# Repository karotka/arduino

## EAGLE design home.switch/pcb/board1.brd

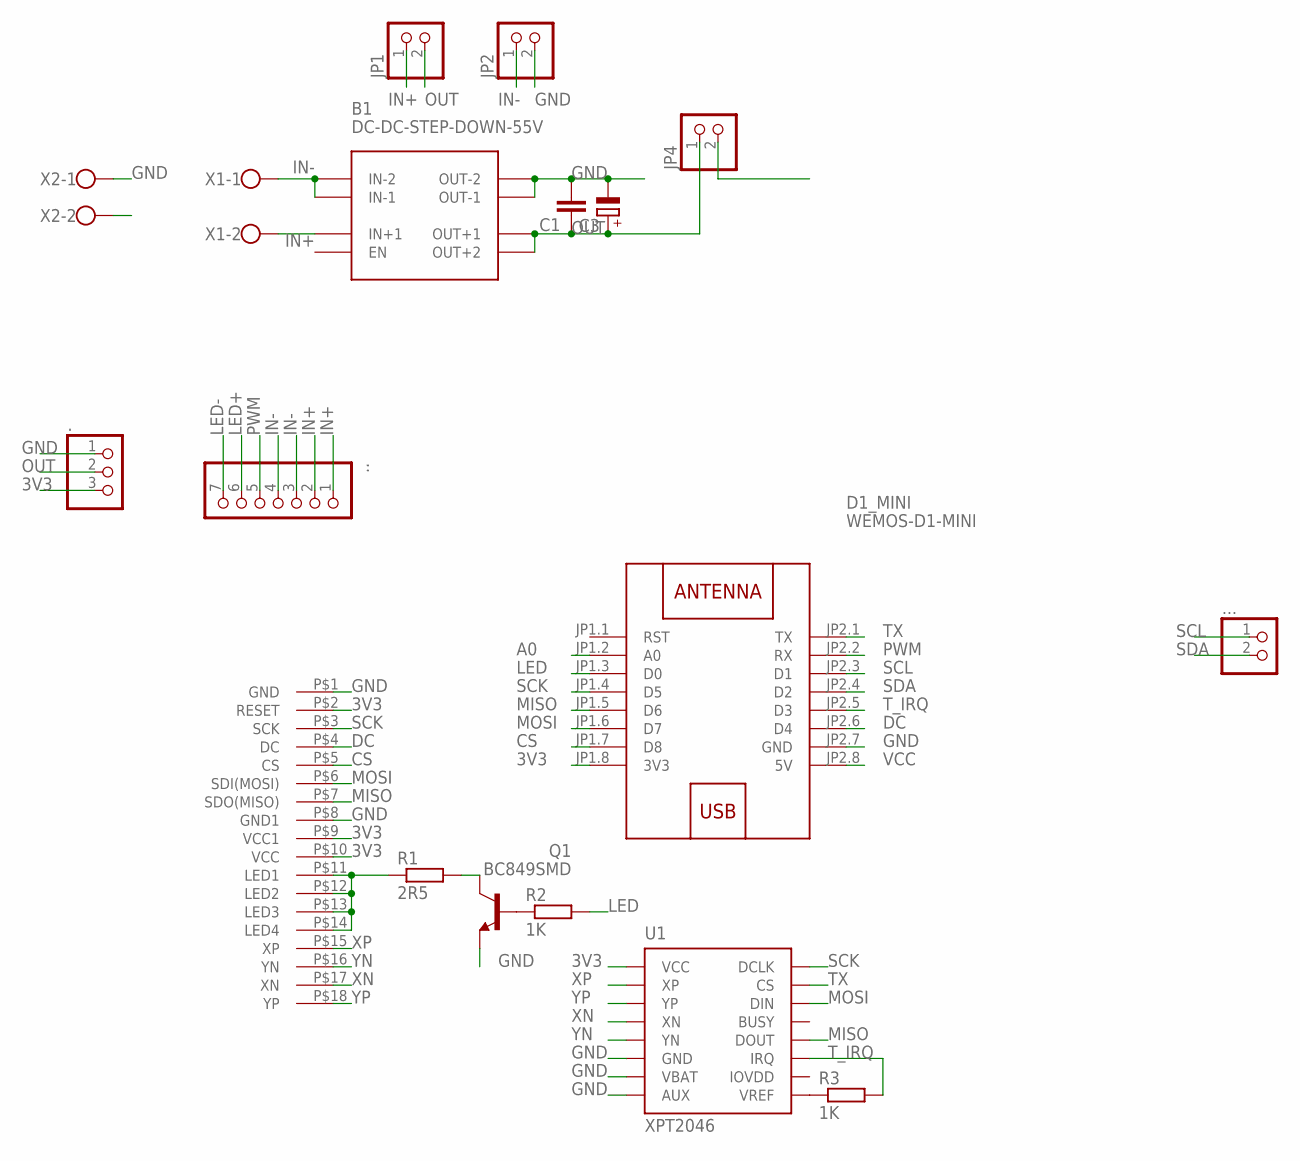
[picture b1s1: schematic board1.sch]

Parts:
.: PINHD-1X3; 1X03
..: PINHD-1X7; 1X07
...: PINHD-1X2; 1X02
B1: DC-DC-STEP-DOWN-55V
C1: C-EUC0805; C0805
C3: CPOL-EUE2-5; E2-5
D1_MINI: WEMOS-D1-MINI
JP1, JP2, JP4: PINHD-1X2; 1X02
Q1: BC849SMD; SOT23-BEC
R1: 2R5; R1210W
R2, R3: 1K; R1210W
U1: XPT2046; TSSOP16
U$2: 2.4TTF; TFT2.4
X1, X2: W237-102

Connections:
3V3: ..3, D1_MINI.JP1.8 (3V3), U1.1 (VCC), U$2.P$2 (RESET), U$2.P$9 (VCC1), U$2.P$10 (VCC)
A0: D1_MINI.JP1.2 (A0), X2.2
CS: D1_MINI.JP1.7 (D8), U$2.P$5 (CS)
DC: D1_MINI.JP2.6 (D4), U$2.P$4 (DC)
GND: ..1, B1.VOUT-1 (OUT-1), B1.VOUT-2 (OUT-2), C1.2, C3.-, D1_MINI.JP2.7 (GND), JP2.2, Q1.E, U1.6 (GND), U1.7 (VBAT), U1.8 (AUX), U$2.P$1 (GND), U$2.P$8 (GND1), X2.1
IN+: ...1, ...2, B1.VIN+ (IN+1), JP1.1, X1.2
IN-: ...3, ...4, B1.VIN-1 (IN-1), B1.VIN-2 (IN-2), JP2.1, X1.1
LED: D1_MINI.JP1.3 (D0), R2.2
LED+: ...6
LED-: ...7
MISO: D1_MINI.JP1.5 (D6), U1.12 (DOUT), U$2.P$7 (SDO(MISO))
MOSI: D1_MINI.JP1.6 (D7), U1.14 (DIN), U$2.P$6 (SDI(MOSI))
unnamed: R1.1, U$2.P$11 (LED1), U$2.P$12 (LED2), U$2.P$13 (LED3), U$2.P$14 (LED4)
unnamed: Q1.C, R1.2
unnamed: Q1.B, R2.1
unnamed: R3.1, U1.9 (VREF)
OUT: ..2, B1.VOUT+1 (OUT+1), B1.VOUT+2 (OUT+2), C1.1, C3.+, JP1.2, JP4.1
PWM: ...5, D1_MINI.JP2.2 (RX)
SCK: D1_MINI.JP1.4 (D5), U1.16 (DCLK), U$2.P$3 (SCK)
SCL: ....1, D1_MINI.JP2.3 (D1)
SDA: ....2, D1_MINI.JP2.4 (D2)
TX: D1_MINI.JP2.1 (TX), U1.15 (CS)
T_IRQ: D1_MINI.JP2.5 (D3), R3.2, U1.11 (IRQ)
VCC: D1_MINI.JP2.8 (5V), JP4.2
XN: U1.4 (XN), U$2.P$17 (XN)
XP: U1.2 (XP), U$2.P$15 (XP)
YN: U1.5 (YN), U$2.P$16 (YN)
YP: U1.3 (YP), U$2.P$18 (YP)

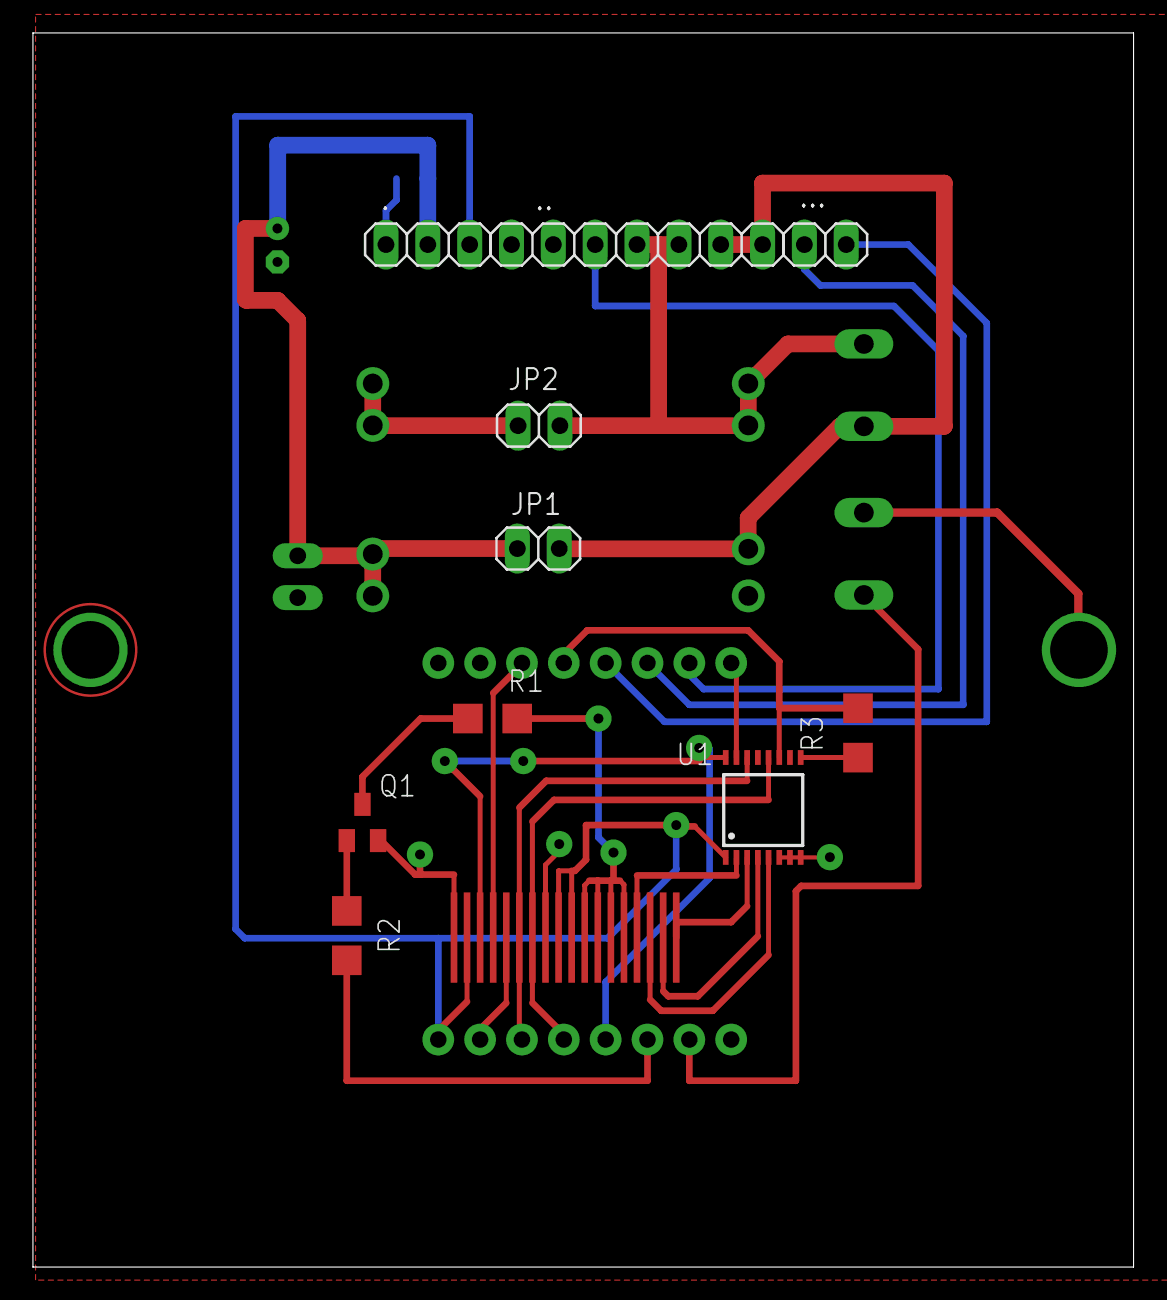
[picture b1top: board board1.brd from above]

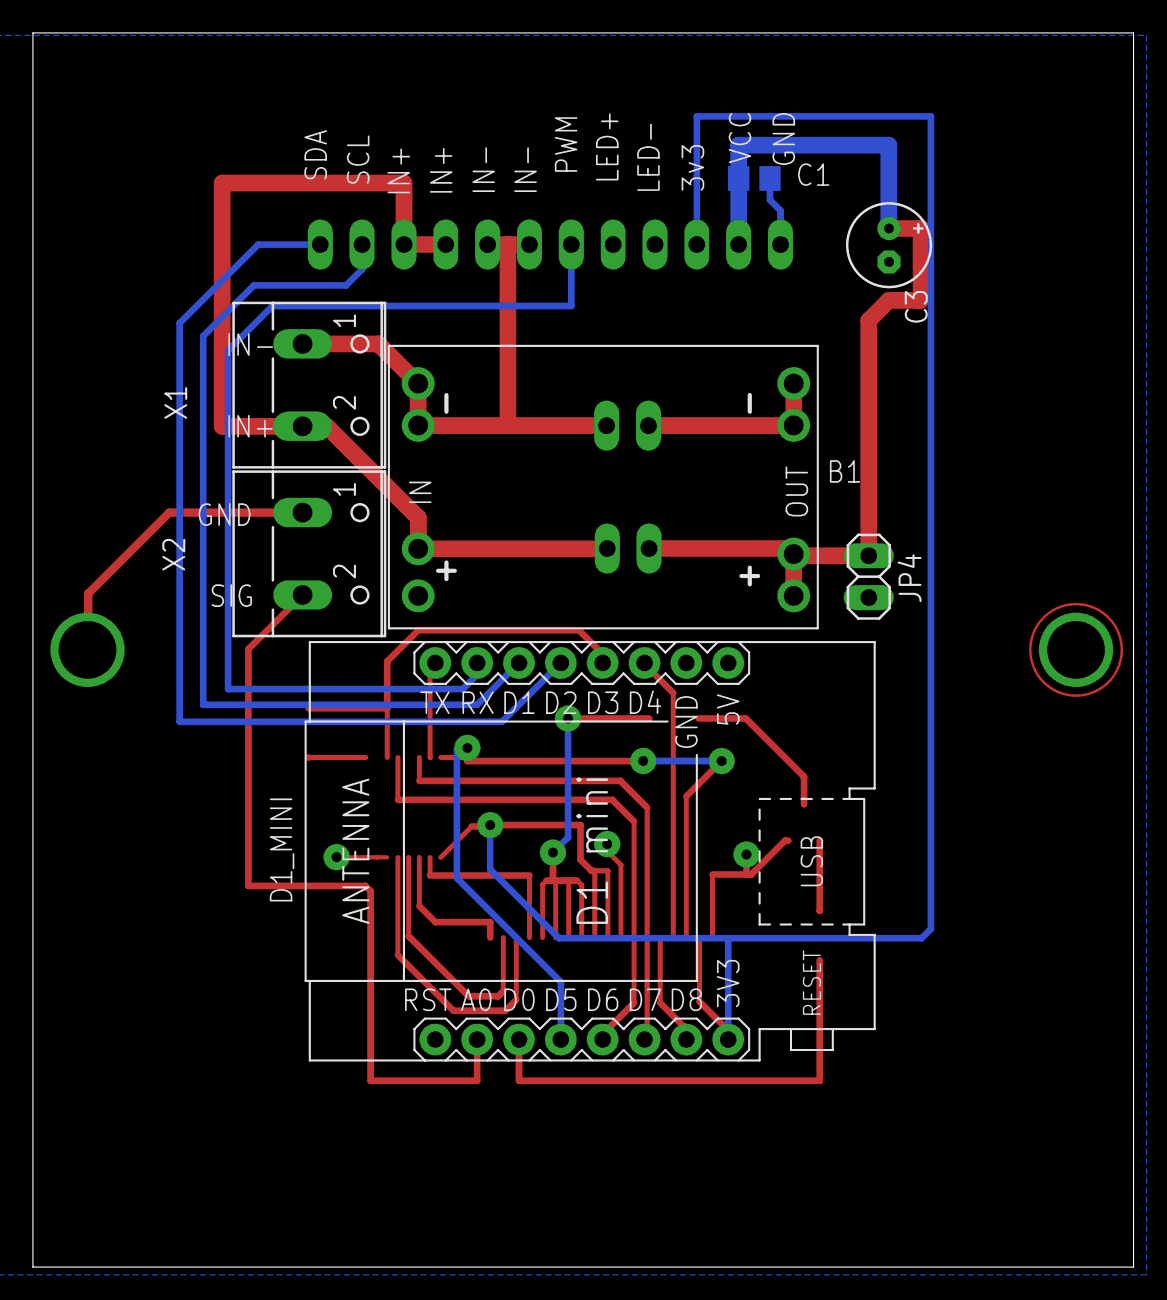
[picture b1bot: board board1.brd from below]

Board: 2 copper layers, 66.8 x 74.9 mm, 18 parts (7 on the bottom side), 26 nets.

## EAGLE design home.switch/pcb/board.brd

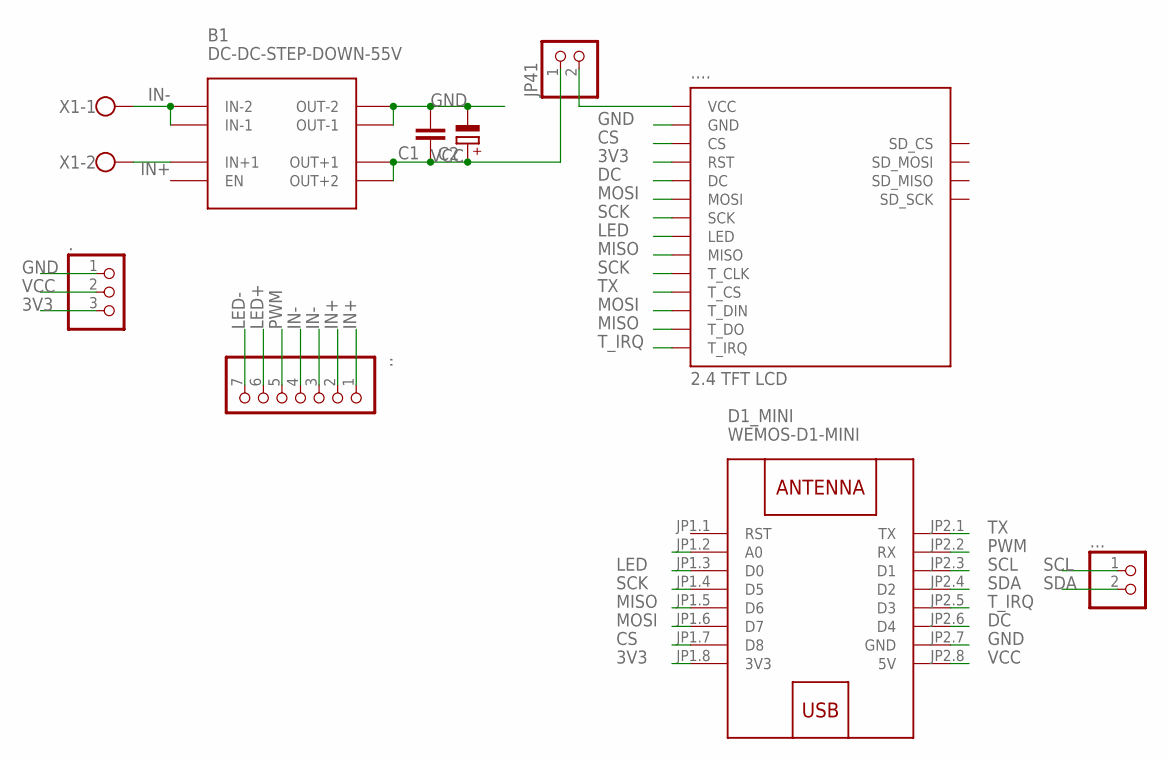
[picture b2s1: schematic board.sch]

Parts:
.: PINHD-1X3; 1X03
..: PINHD-1X7; 1X07
...: PINHD-1X2; 1X02
....: 2.2_TFT_LCD
B1: DC-DC-STEP-DOWN-55V
C1: C-EUC0805; C0805
C2: CPOL-EUE2-5; E2-5
D1_MINI: WEMOS-D1-MINI
JP41: PINHD-1X2; 1X02
X1: W237-102

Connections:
3V3: ..3, .....RST, D1_MINI.JP1.8 (3V3)
CS: .....CS, D1_MINI.JP1.7 (D8)
DC: .....DC, D1_MINI.JP2.6 (D4)
GND: ..1, .....GND, B1.VOUT-1 (OUT-1), B1.VOUT-2 (OUT-2), C1.2, C2.-, D1_MINI.JP2.7 (GND)
IN+: ...1, ...2, B1.VIN+ (IN+1), X1.2
IN-: ...3, ...4, B1.VIN-1 (IN-1), B1.VIN-2 (IN-2), X1.1
LED: .....LED, D1_MINI.JP1.3 (D0)
LED+: ...6
LED-: ...7
MISO: .....MISO, .....T_DO, D1_MINI.JP1.5 (D6)
MOSI: .....MOSI, .....T_DIN, D1_MINI.JP1.6 (D7)
unnamed: .....VCC, JP41.2
PWM: ...5, D1_MINI.JP2.2 (RX)
SCK: .....SCK, .....T_CLK, D1_MINI.JP1.4 (D5)
SCL: ....1, D1_MINI.JP2.3 (D1)
SDA: ....2, D1_MINI.JP2.4 (D2)
TX: .....T_CS, D1_MINI.JP2.1 (TX)
T_IRQ: .....T_IRQ, D1_MINI.JP2.5 (D3)
VCC: ..2, B1.VOUT+1 (OUT+1), B1.VOUT+2 (OUT+2), C1.1, C2.+, D1_MINI.JP2.8 (5V), JP41.1

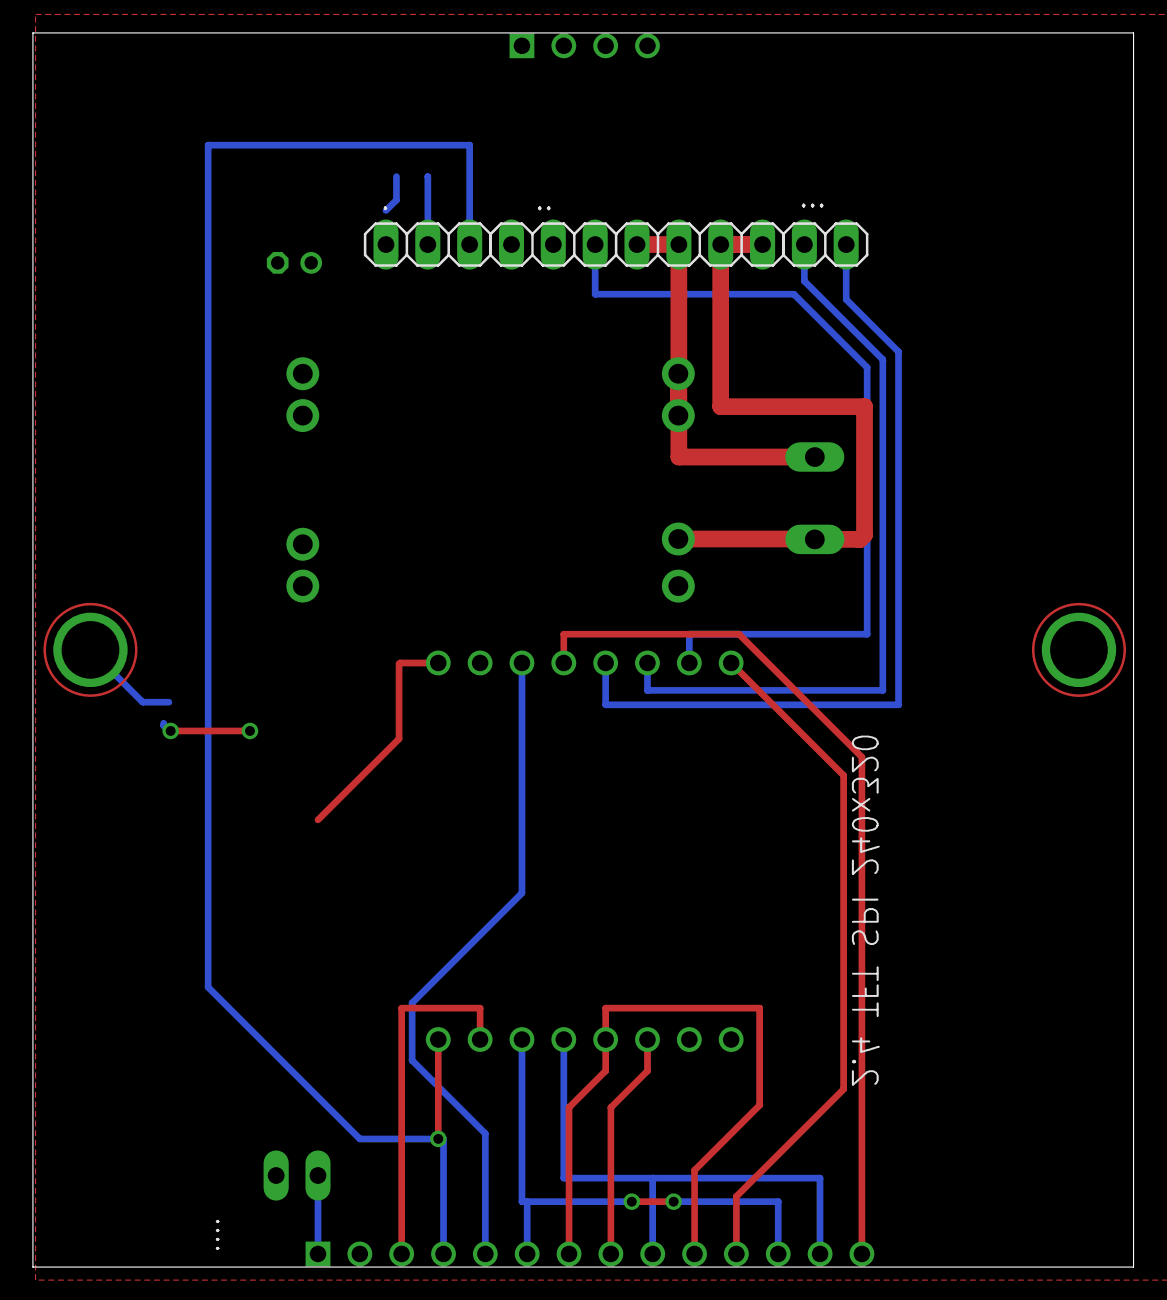
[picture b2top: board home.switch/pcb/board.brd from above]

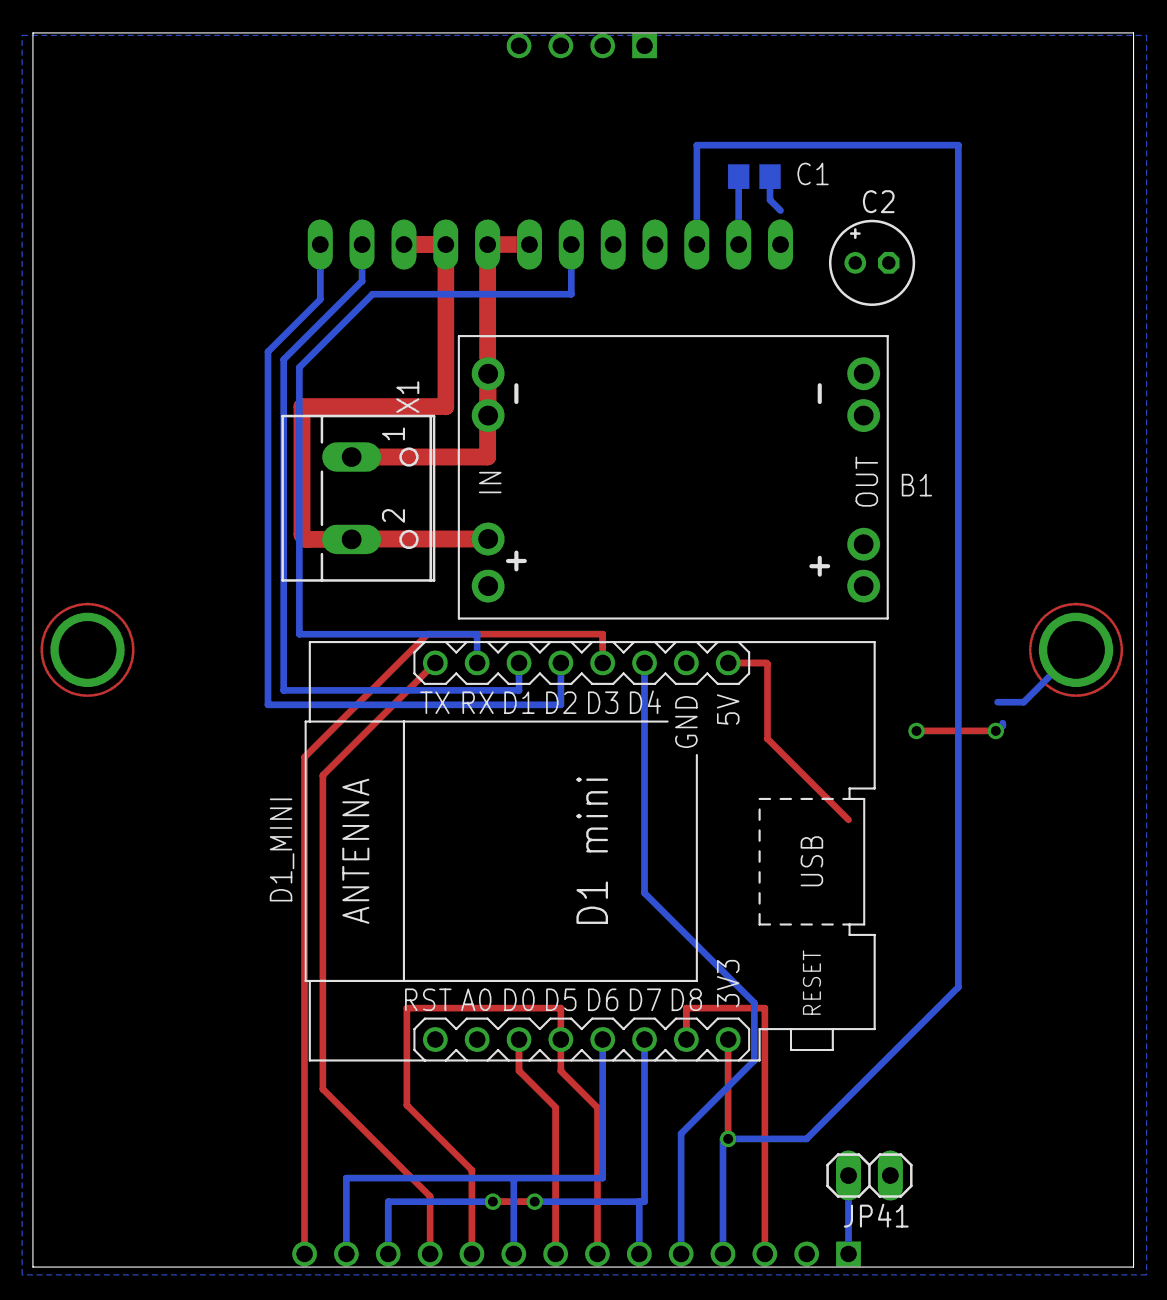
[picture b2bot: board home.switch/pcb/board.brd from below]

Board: 2 copper layers, 66.8 x 74.9 mm, 10 parts (6 on the bottom side), 17 nets.

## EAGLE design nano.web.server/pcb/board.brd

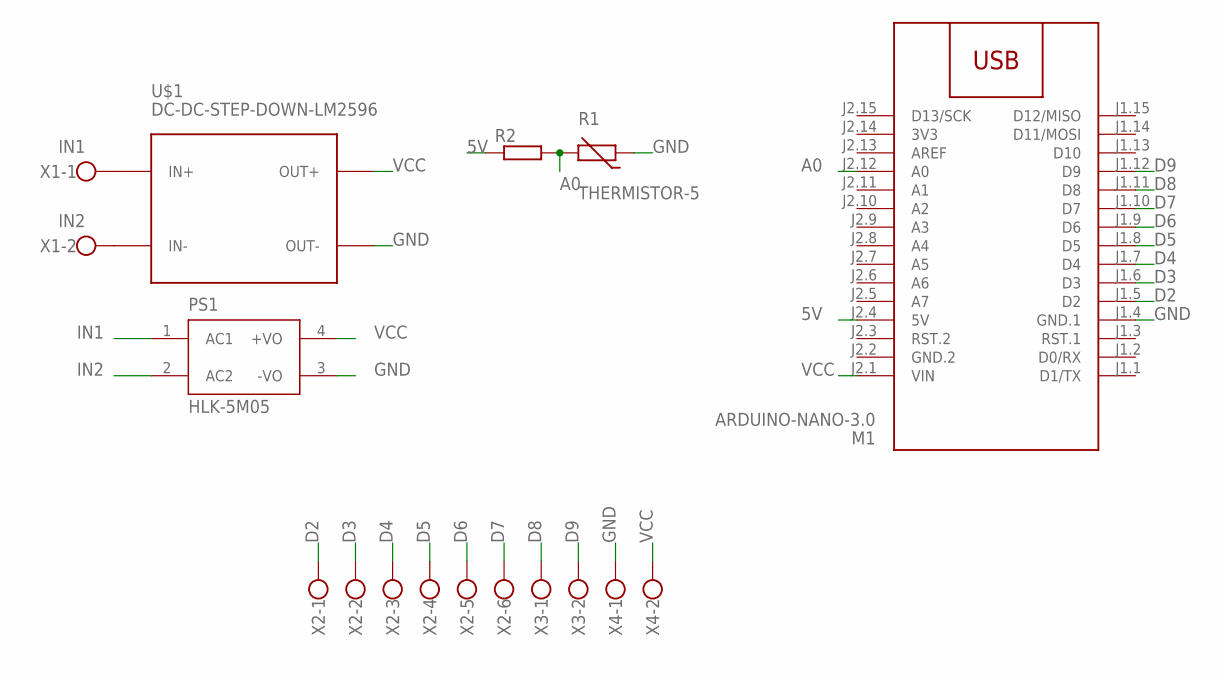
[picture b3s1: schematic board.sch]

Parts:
M1: ARDUINO-NANO-3.0
PS1: HLK-5M05; CONV_HLK-5M05
R1: THERMISTOR-5; R-5
R2: R-EU_0207/10; 0207/10
U$1: DC-DC-STEP-DOWN-LM2596
X1, X3, X4: W237-102
X2: W237-136

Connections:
3V3: M1.J2.14 (3V3)
5V: M1.J2.4 (5V), R2.1
A0: M1.J2.12 (A0), R1.2, R2.2
D2: M1.J1.5 (D2), X2.1
D3: M1.J1.6 (D3), X2.2
D4: M1.J1.7 (D4), X2.3
D5: M1.J1.8 (D5), X2.4
D6: M1.J1.9 (D6), X2.5
D7: M1.J1.10 (D7), X2.6
D8: M1.J1.11 (D8), X3.1
D9: M1.J1.12 (D9), X3.2
GND: M1.J1.4 (GND.1), PS1.3 (-VO), R1.1, U$1.OUT-, X4.1
GND.2: M1.J2.2 (GND.2)
IN1: PS1.1 (AC1), U$1.IN+, X1.1
IN2: PS1.2 (AC2), U$1.IN-, X1.2
VCC: M1.J2.1 (VIN), PS1.4 (+VO), U$1.OUT+, X4.2

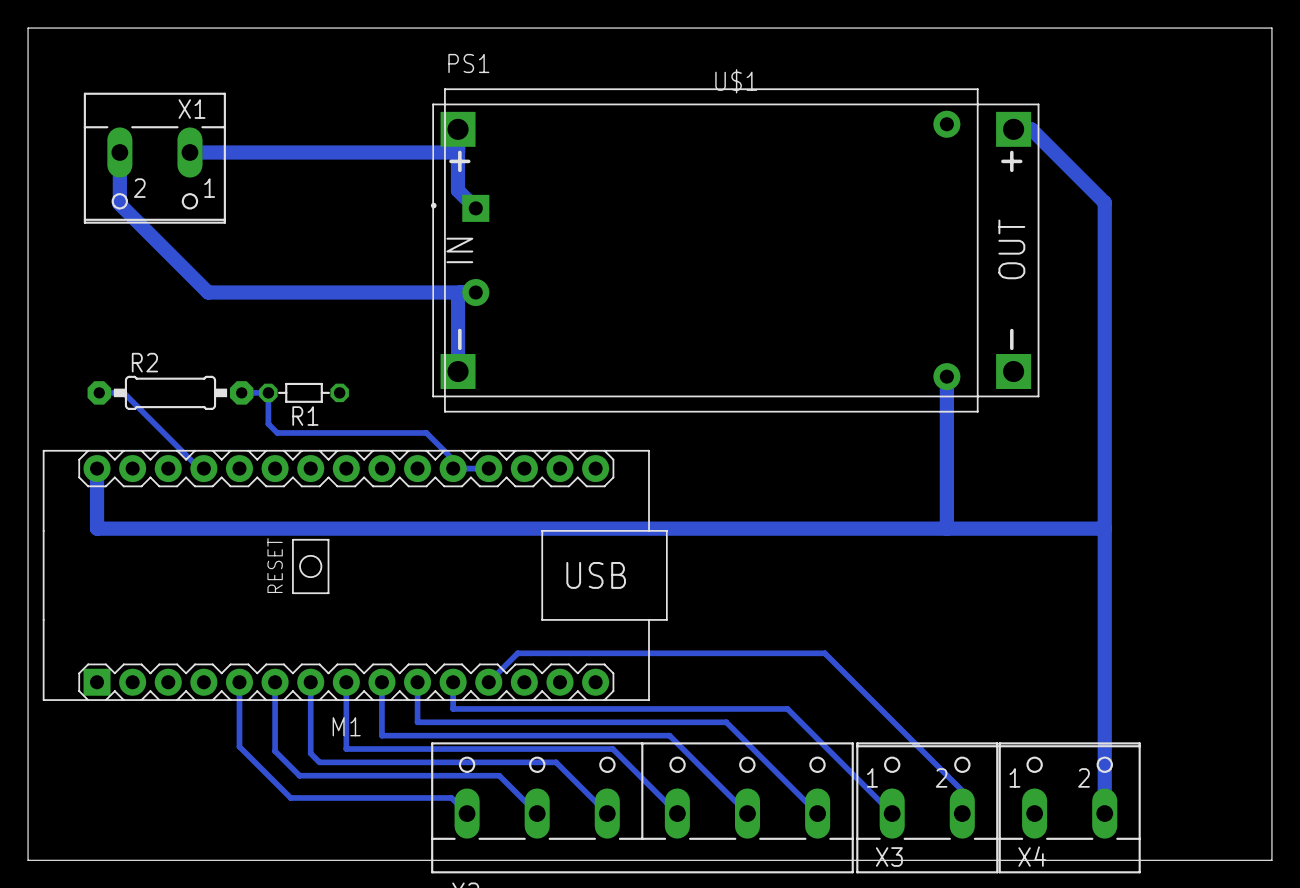
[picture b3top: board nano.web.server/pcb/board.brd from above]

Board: 2 copper layers, 88.7 x 59.4 mm, 9 parts (0 on the bottom side), 14 nets.

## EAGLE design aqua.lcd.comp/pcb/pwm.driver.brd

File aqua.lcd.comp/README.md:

Aquarium computer
=================

Properties
----------

2018-08-21:
	Actually I working on new shield for Arduino Mega with serial display connection, web interface with (Microsoft Metro design) Esp8266 and other new features 

- Computer for manage aquarium lights and measurment the tempereature

It is possible to set many modes of change light color in time.

- Date and time

It containts on board RTC clock for date and time measurment

- Touch display

You can manage all function by touch display

- 6 independent light channels with PWM

you can manage 6 lights channel for to set you onw 12V LED lights

- 8 independent light modes

can manage your onw day lights modes

- rele for switching 230V for CO2 valve switching

- 3 independent sensor for temperature measurment

3 thermistor channels can measure temperature in different position in aquarium

- 1 onboard sensor for temperature measurment

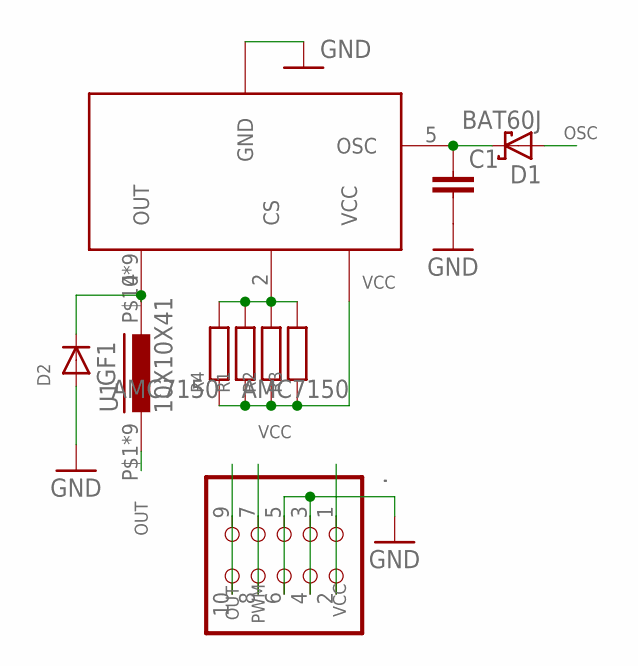
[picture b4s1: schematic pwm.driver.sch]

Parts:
.: PINHD-2X5; 2X05
AMC7150: AMC7150; TO-252-5L
C1: C-EU025-024X044; C025-024X044
D1: BAT60J; SOD323_ST
D2: GF1; SMA-DO214AC
R1, R2, R3, R4: R-EU_R1206; R1206
U1: 10X10X41; 10X10X4

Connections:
CS: AMC7150.2 (CS), R1.2, R2.2, R3.2, R4.2
GND: ..3, ..4, ..5, ..6, AMC7150.3 (GND), AMC7150.TAB (GND), C1.2, D2.A
unnamed: AMC7150.4 (OUT), D2.K (C), U1.P$10 (2), U1.P$11 (2), U1.P$12 (2), U1.P$13 (2), U1.P$14 (2), U1.P$15 (2), U1.P$16 (2), U1.P$17 (2), U1.P$18 (2)
OSC: AMC7150.5 (OSC), C1.1, D1.C
OUT: ..9, ..10, U1.P$1 (1), U1.P$2 (1), U1.P$3 (1), U1.P$4 (1), U1.P$5 (1), U1.P$6 (1), U1.P$7 (1), U1.P$8 (1), U1.P$9 (1)
PWM: ..7, ..8, D1.A
VCC: ..1, ..2, AMC7150.1 (VCC), R1.1, R2.1, R3.1, R4.1

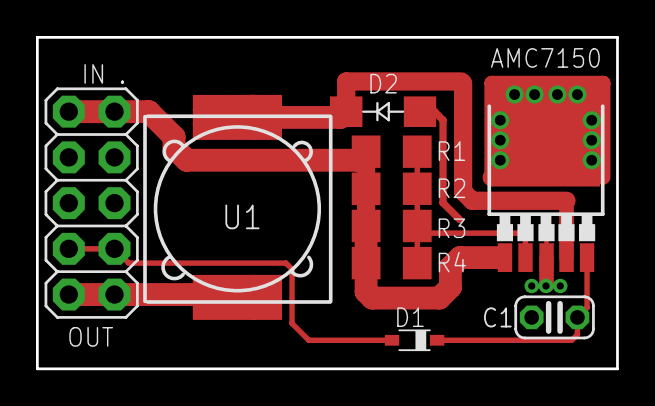
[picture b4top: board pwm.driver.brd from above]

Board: 2 copper layers, 32.2 x 18.4 mm, 10 parts (0 on the bottom side), 7 nets.

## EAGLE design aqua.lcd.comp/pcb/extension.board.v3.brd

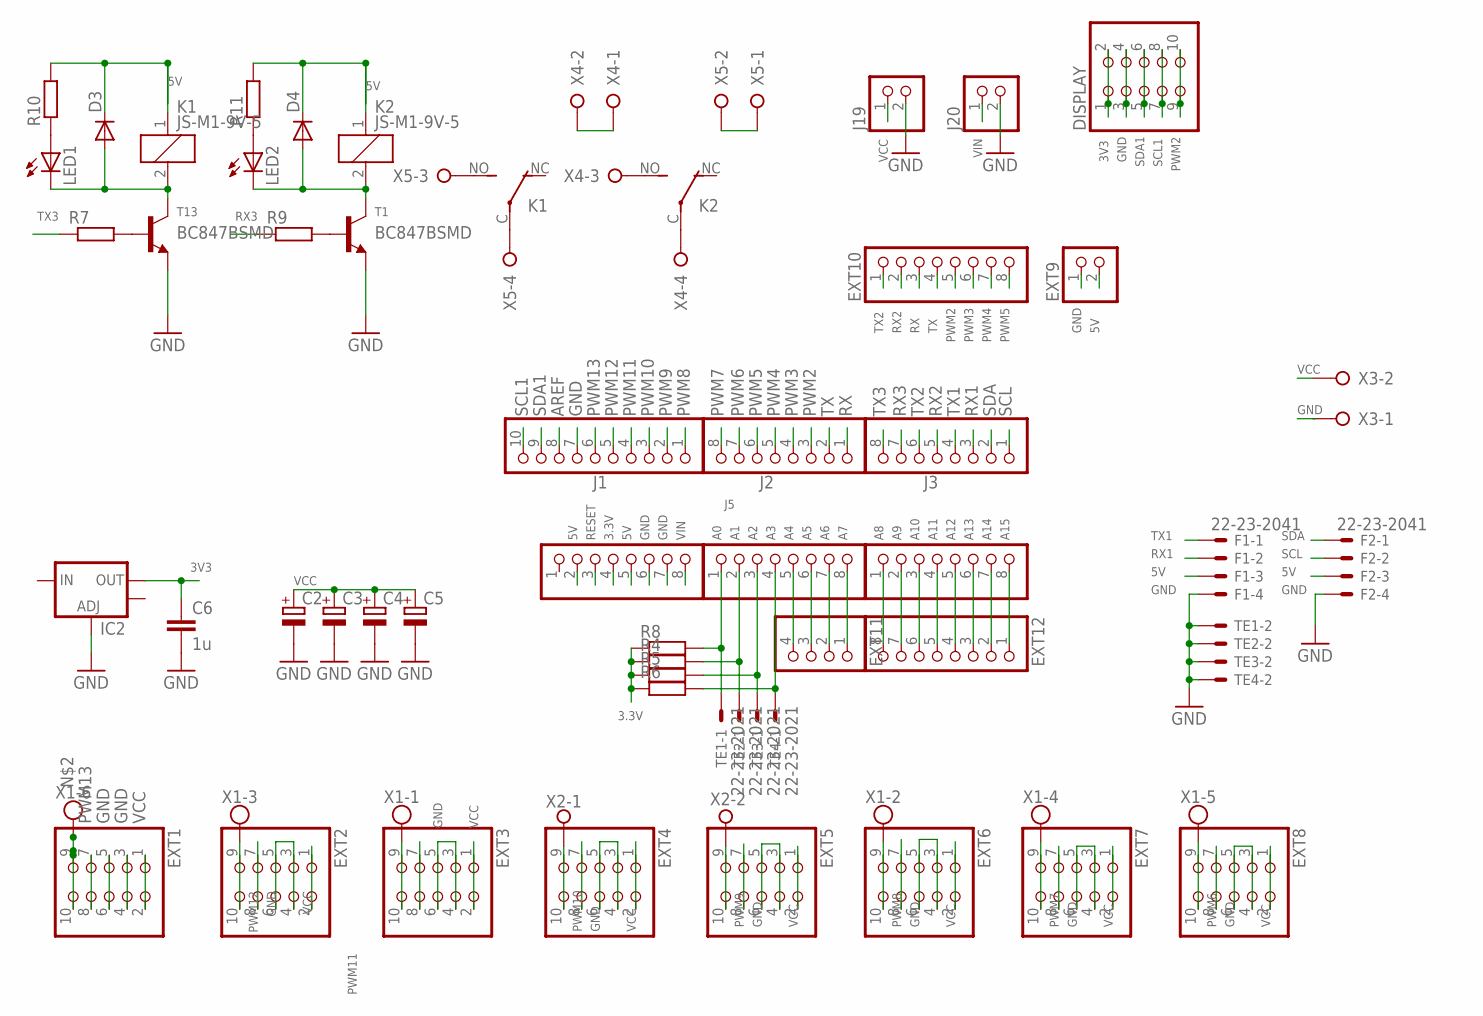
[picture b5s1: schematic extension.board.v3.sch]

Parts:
C2, C3, C4, C5: CPOL-EUE2.5-7; E2,5-7
C6: 1u; C0805
D3, D4: DIODE-DO-214AC; DO-214AC
DISPLAY: PINHD-2X5; 2X05
EXT1, EXT2, EXT3, EXT4, EXT5, EXT6, EXT7, EXT8: PINHD-2X5; 2X05
EXT9: PINHD-1X2; 1X02
EXT10, EXT12: PINHD-1X8; 1X08
EXT11: PINHD-1X4; 1X04
F1, F2: 22-23-2041
IC2: V_REG_LM1117SOT223; SOT223
J1: PINHD-1X10; 1X10
J2, J3, J4, J5, J6: PINHD-1X8; 1X08
J19, J20: PINHD-1X2; 1X02
K1, K2: JS-M1-9V-5; JS-M
LED1, LED2: LEDSML1206; SML1206
R4, R5, R6, R7, R8, R9, R10, R11: R-EU_R1206; R1206
T1, T13: BC847BSMD; SOT23
TE1, TE2, TE3, TE4: 22-23-2021
X1: W237-6
X2, X3: W237-02P; W237-132
X4, X5: W237-04P; W237-4P

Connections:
3.3V: J6.4, R4.1, R5.1, R6.1, R8.1
3V3: C6.1, DISPLAY.1, DISPLAY.2, IC2.2 (OUT)
5V: D3.C, D4.C, EXT9.2, F1.3, F2.3, J6.2, J6.5, K1.1, K2.1, R10.2, R11.2
A0: J5.1, R8.2, TE1.1
A1: J5.2, R4.2, TE2.1
A2: J5.3, R5.2, TE3.1
A3: J5.4, R6.2, TE4.1
A4: EXT11.4, J5.5
A5: EXT11.3, J5.6
A6: EXT11.2, J5.7
A7: EXT11.1, J5.8
A8: EXT12.8, J4.1
A9: EXT12.7, J4.2
A10: EXT12.6, J4.3
A11: EXT12.5, J4.4
A12: EXT12.4, J4.5
A13: EXT12.3, J4.6
A14: EXT12.2, J4.7
A15: EXT12.1, J4.8
AREF: J1.8
GND: C2.-, C3.-, C4.-, C5.-, C6.2, DISPLAY.3, DISPLAY.4, EXT1.3, EXT1.4, EXT1.5, EXT1.6, EXT2.3, EXT2.4, EXT2.5, EXT2.6, EXT3.3, EXT3.4, EXT3.5, EXT3.6, EXT4.3, EXT4.4, EXT4.5, EXT4.6, EXT5.3, EXT5.4, EXT5.5, EXT5.6, EXT6.3, EXT6.4, EXT6.5, EXT6.6, EXT7.3, EXT7.4, EXT7.5, EXT7.6, EXT8.3, EXT8.4, EXT8.5, EXT8.6, EXT9.1, F1.4, F2.4, IC2.1 (ADJ), J1.7, J6.6, J6.7, J19.2, J20.2, T1.2 (E), T13.2 (E), TE1.2, TE2.2, TE3.2, TE4.2, X3.1
unnamed: EXT1.9, EXT1.10, X1.6
unnamed: EXT8.9, EXT8.10, X1.5
unnamed: EXT7.9, EXT7.10, X1.4
unnamed: EXT2.9, EXT2.10, X1.3
unnamed: EXT6.9, EXT6.10, X1.2
unnamed: EXT3.9, EXT3.10, X1.1
unnamed: EXT5.9, EXT5.10, X2.2
unnamed: EXT4.9, EXT4.10, X2.1
unnamed: R7.2, T13.1 (B)
unnamed: D4.A, K2.2, LED2.C, T1.3 (C)
unnamed: R9.2, T1.1 (B)
unnamed: X4.1, X4.2
unnamed: X5.1, X5.2
unnamed: K2.C, X4.4
unnamed: K1.C, X5.4
unnamed: K2.NO (S), X4.3
unnamed: K1.NO (S), X5.3
unnamed: LED1.A, R10.1
unnamed: LED2.A, R11.1
unnamed: D3.A, K1.2, LED1.C, T13.3 (C)
PWM2: DISPLAY.9, DISPLAY.10, EXT10.5, J2.3
PWM3: EXT10.6, J2.4
PWM4: EXT10.7, J2.5
PWM5: EXT10.8, J2.6
PWM6: EXT8.7, EXT8.8, J2.7
PWM7: EXT7.7, EXT7.8, J2.8
PWM8: EXT6.7, EXT6.8, J1.1
PWM9: EXT5.7, EXT5.8, J1.2
PWM10: EXT4.7, EXT4.8, J1.3
PWM11: EXT3.7, EXT3.8, J1.4
PWM12: EXT2.7, EXT2.8, J1.5
PWM13: EXT1.7, EXT1.8, J1.6
RESET: J6.3
RX: EXT10.3, J2.1
RX1: F1.2, J3.3
RX2: EXT10.2, J3.5
RX3: J3.7, R9.1
SCL: F2.2, J3.1
SCL1: DISPLAY.7, DISPLAY.8, J1.10
SDA: F2.1, J3.2
SDA1: DISPLAY.5, DISPLAY.6, J1.9
TX: EXT10.4, J2.2
TX1: F1.1, J3.4
TX2: EXT10.1, J3.6
TX3: J3.8, R7.1
VCC: C2.+, C3.+, C4.+, C5.+, EXT1.1, EXT1.2, EXT2.1, EXT2.2, EXT3.1, EXT3.2, EXT4.1, EXT4.2, EXT5.1, EXT5.2, EXT6.1, EXT6.2, EXT7.1, EXT7.2, EXT8.1, EXT8.2, J19.1, X3.2
VIN: J6.8, J20.1

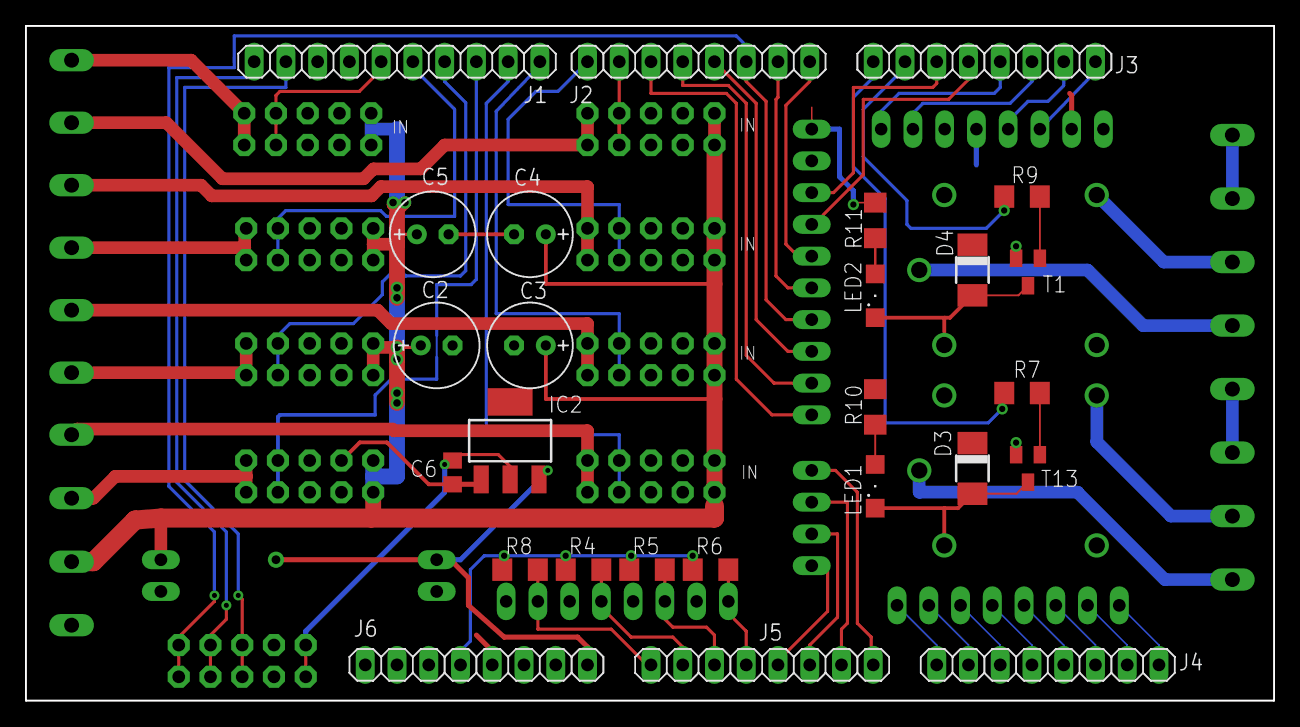
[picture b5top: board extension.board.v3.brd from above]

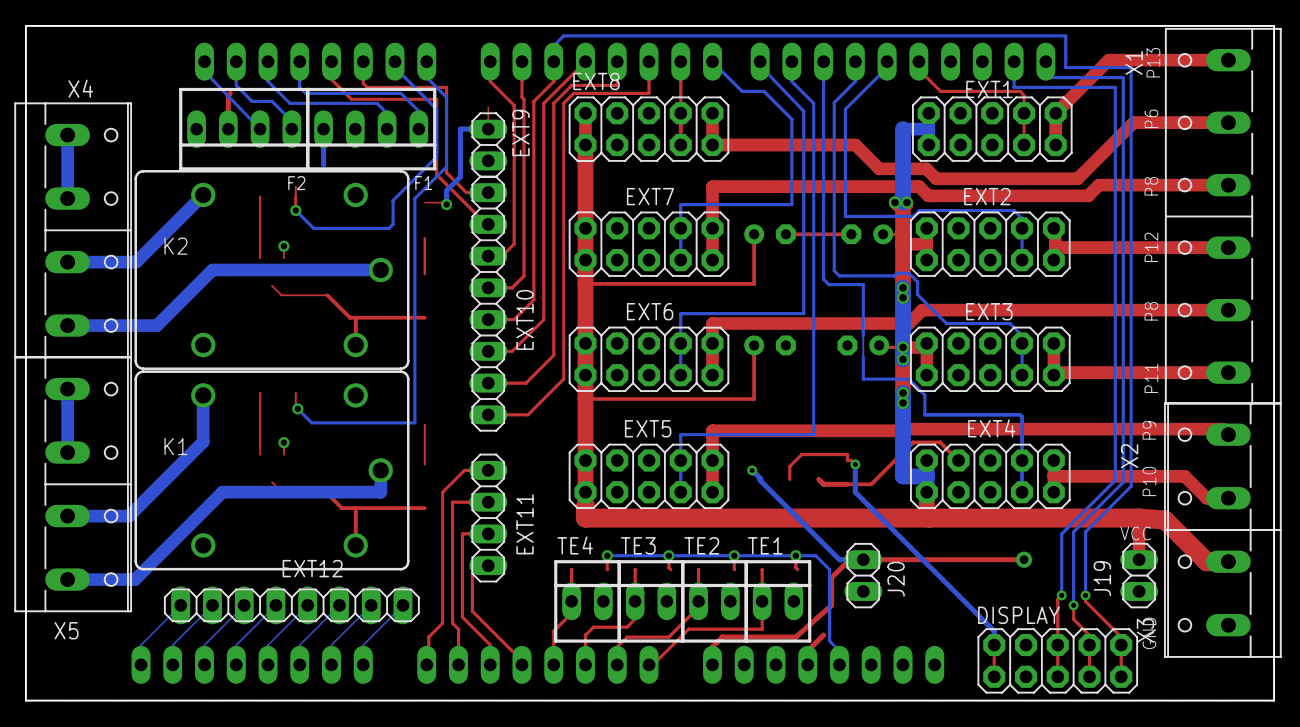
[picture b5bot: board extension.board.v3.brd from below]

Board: 2 copper layers, 99.9 x 54.0 mm, 54 parts (28 on the bottom side), 66 nets.

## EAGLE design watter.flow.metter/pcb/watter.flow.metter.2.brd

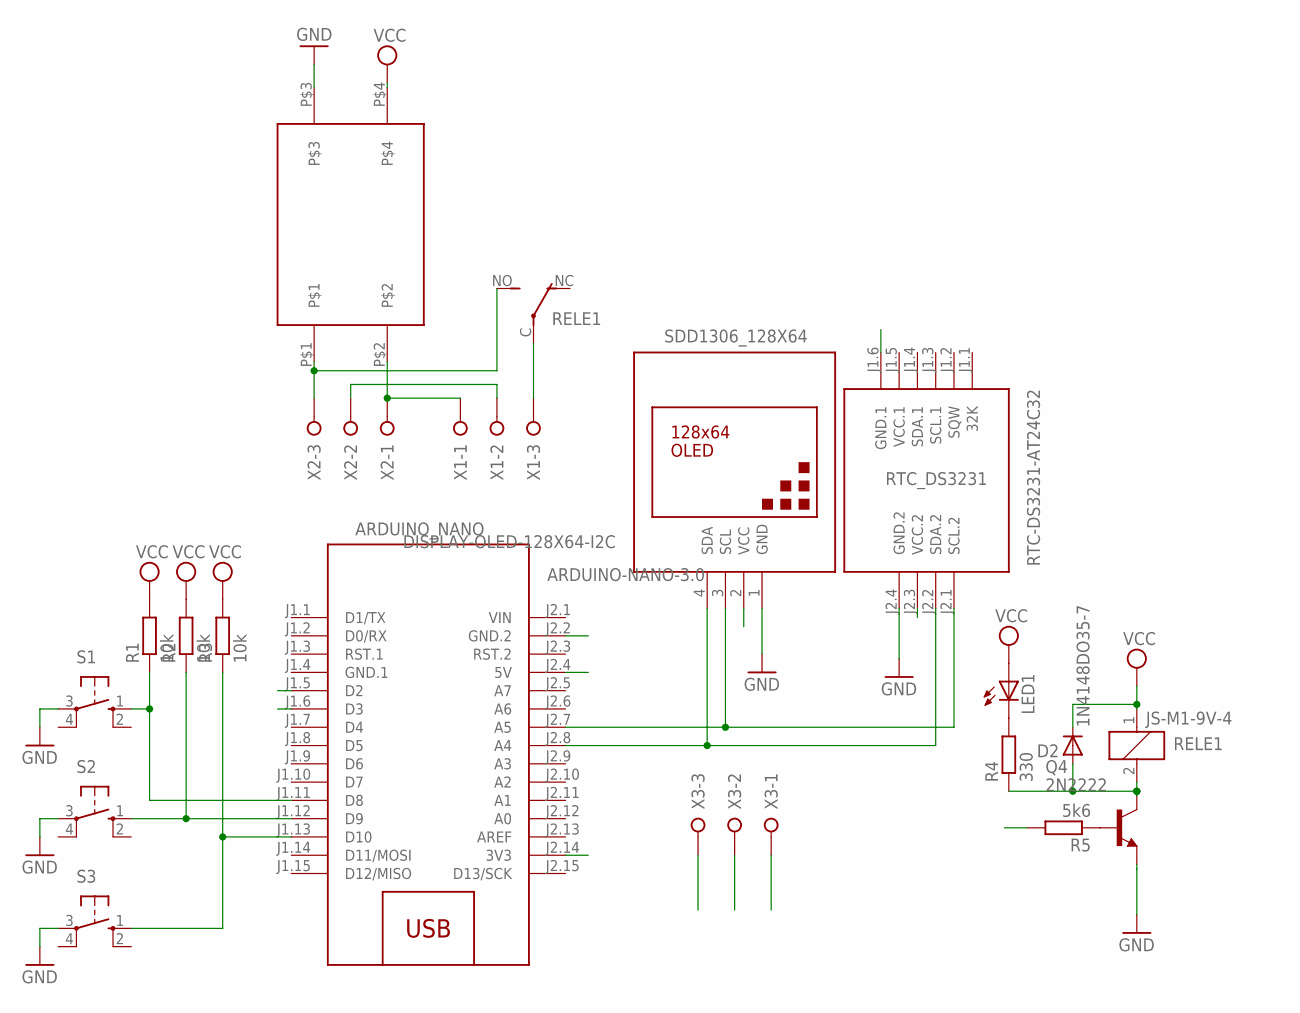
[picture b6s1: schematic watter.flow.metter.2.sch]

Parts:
ARDUINO_NANO: ARDUINO-NANO-3.0
D2: 1N4148DO35-7; DO35-7
LED1: LED3MM
Q4: 2N2222; TO92
R1, R2, R3: 10k; 0207/10
R4: 330; 0207/10
R5: 5k6; 0207/10
RELE1: JS-M1-9V-4; JS-M
RTC_DS3231: RTC-DS3231-AT24C32
S1, S2, S3: 10-XX; B3F-10XX
SDD1306_128X64: DISPLAY-OLED-128X64-I2C
U$6: HLK-PM01
X1, X2, X3: W237-3E

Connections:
3.3V: ARDUINO_NANO.J2.14 (3V3), RTC_DS3231.J2.3 (VCC.2), SDD1306_128X64.2 (VCC)
D2: ARDUINO_NANO.J1.5 (D2), X3.2
D3: ARDUINO_NANO.J1.6 (D3), R5.2
GND: ARDUINO_NANO.J2.2 (GND.2), Q4.3 (E), RTC_DS3231.J2.4 (GND.2), S1.3, S2.3, S3.3, SDD1306_128X64.1 (GND), U$6.P$3, X3.1
GND.1: ARDUINO_NANO.J1.4 (GND.1)
unnamed: RELE1.C, X1.3
unnamed: ARDUINO_NANO.J1.11 (D8), R1.1, S1.1 (S)
unnamed: U$6.P$2, X1.1, X2.1
unnamed: RELE1.NO (S), U$6.P$1, X2.3
unnamed: ARDUINO_NANO.J1.12 (D9), R2.1, S2.1 (S)
unnamed: ARDUINO_NANO.J1.13 (D10), R3.1, S3.1 (S)
unnamed: Q4.2 (B), R5.1
unnamed: LED1.K (C), R4.2
unnamed: X1.2, X2.2
unnamed: D2.A, Q4.1 (C), R4.1, RELE1.2
SCL: ARDUINO_NANO.J2.7 (A5), RTC_DS3231.J2.1 (SCL.2), SDD1306_128X64.3 (SCL)
SDA: ARDUINO_NANO.J2.8 (A4), RTC_DS3231.J2.2 (SDA.2), SDD1306_128X64.4 (SDA)
VCC: ARDUINO_NANO.J2.4 (5V), D2.C, LED1.A, R1.2, R2.2, R3.2, RELE1.1, U$6.P$4, X3.3
VCC.1: RTC_DS3231.J1.5 (VCC.1)
VIN: ARDUINO_NANO.J2.1 (VIN)

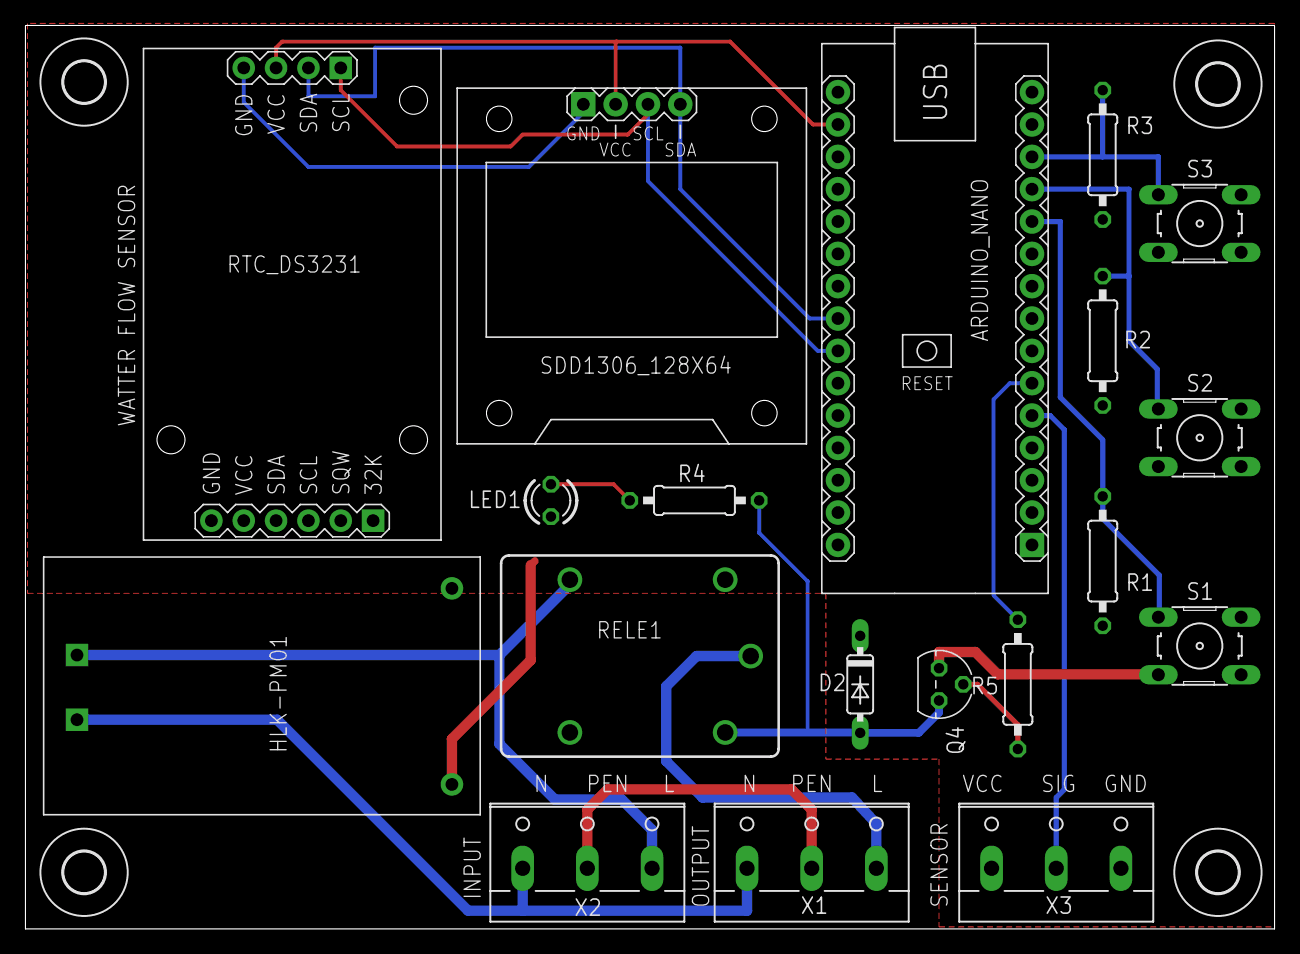
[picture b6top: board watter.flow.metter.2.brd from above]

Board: 2 copper layers, 98.1 x 71.0 mm, 23 parts (0 on the bottom side), 17 nets.

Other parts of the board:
U$3, U$4, U$7, U$8: 3,2

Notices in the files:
parts and their libraries:
sparkfun: Licensing: CC v3.0 Share-Alike You are welcome to use this library for commercial purposes.
diy-modules: Released under the Creative Commons Attribution 4.0 International License: http://creativecommons.org/licenses/by/4.0
